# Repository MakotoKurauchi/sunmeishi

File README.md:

# sun meishi

## これは

Kailh Sun Switchを使用した名刺サイズのマクロパッドです。
ロータリーエンコーダもLEDが入っているのでカラフルに光ります。

## 課題

現状でも動作には問題ありませんが、LEDドライバをISSIのデバイスに変えたいと思っています。

## Data
* [Firmware](https://github.com/MakotoKurauchi/qmk_firmware/tree/sunmeishi/keyboards/sunmeishi)
* [PCB Data](/PCB)

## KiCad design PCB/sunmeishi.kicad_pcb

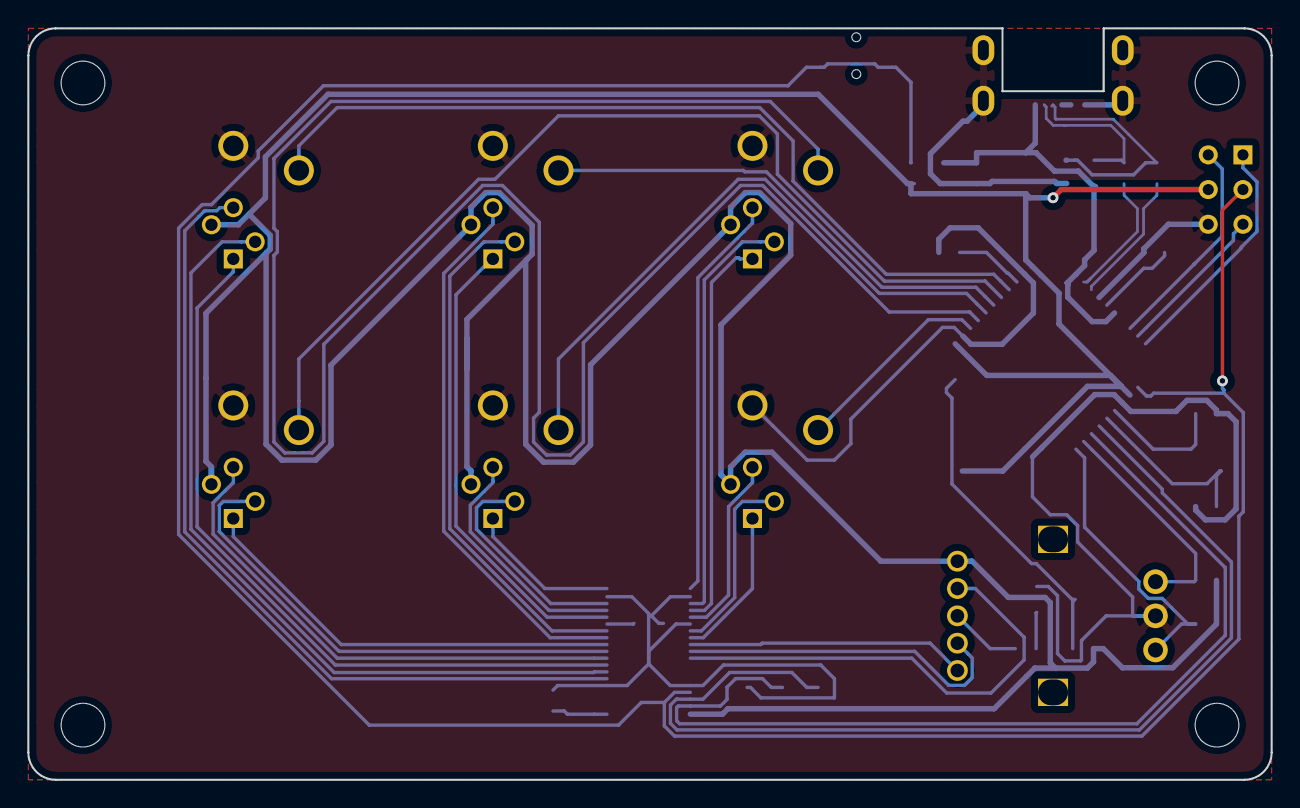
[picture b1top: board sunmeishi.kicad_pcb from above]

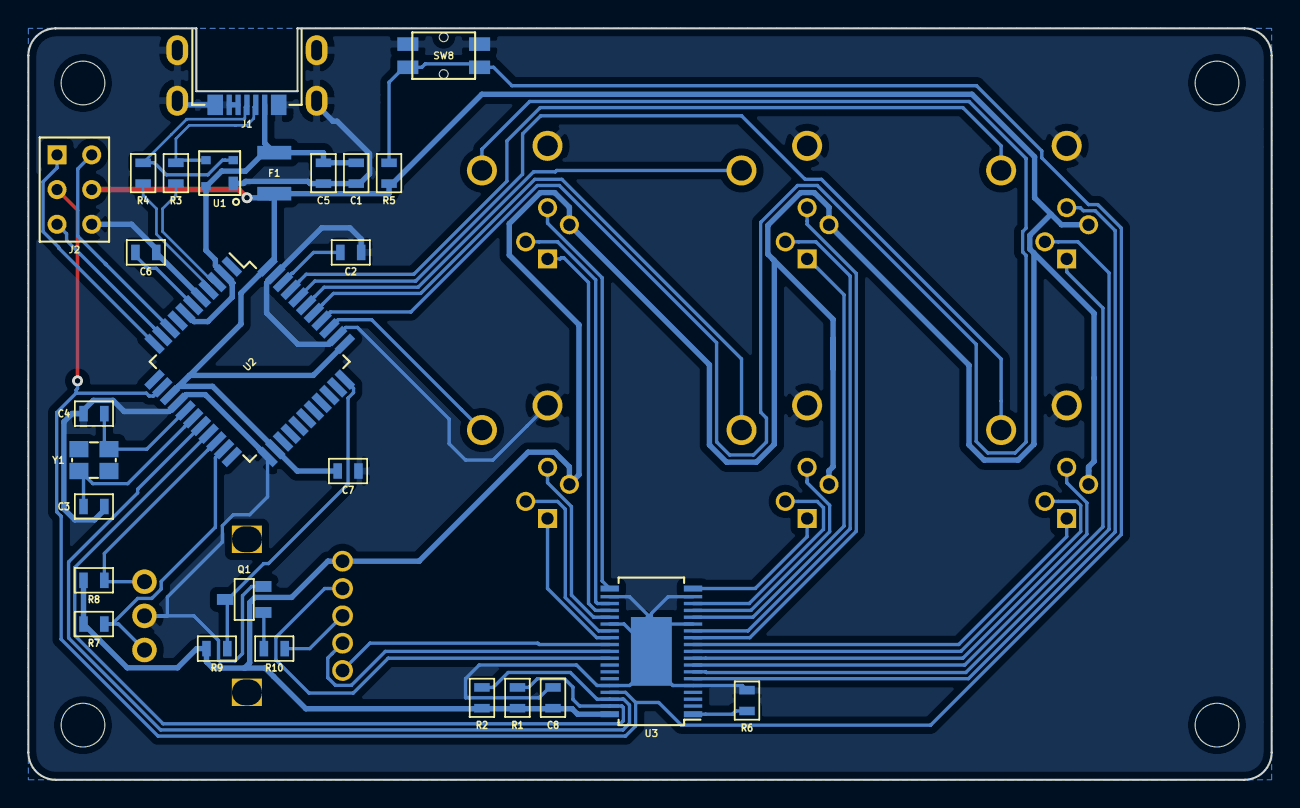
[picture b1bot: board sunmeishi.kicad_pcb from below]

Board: 2 copper layers, 91.0 x 55.0 mm, 44 parts (27 on the bottom side), 50 nets.

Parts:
C1: 10u; SM0603_C
C2, C5, C7, C8: 0.1u; SM0603_C
C3, C4: 22p; SM0603_C
C6: 1u; SM0603_C
F1: FUSE; POLYSWITCH_MICRO_SMD
HOLE_3M, HOLE_3M#2, HOLE_3M#3, HOLE_3M#4: VAL**; HOLE_3M
J1: USB_3; USB_MicroB_609-4049-1-ND
J2: Conn_02x03_Top_Bottom; MY_SIL-2x3
LED1, LED2, LED3, LED4, LED5, LED6: F_LED_A_MINI3; BZPG1583-08002-A1
Q1: 2SC2712
R1, R2: 4.7K; SM0603_R
R3, R4: 22; SM0603_R
R5, R7, R8: 10K; SM0603_R
R6: 2K; SM0603_R
R9, R10: 1K; SM0603_R
SW1, SW2, SW3, SW4, SW5, SW6: SW_Push_45deg; CPG1511B01D03
SW7: EC12PLRGBSDVBF-D-25K-24-24C-61
SW8: SW_Push; TACTSWITCH_ATD-THAF01_SMD
U1: PRTR5V0U2X; SOT143B
U2: ATMEGA32U4_; LQFP-44_10x10mm_Pitch0.8mm
U3: PCA9956ATW; PCA9956BTW
Y1: Crystal; FA-238

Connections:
+5V: C7.1, C8.1, F1.2, J2.4, LED1.2, LED2.2, LED3.2, LED4.2, LED5.2, LED6.2, R1.1, R2.1, R5.2, R7.1, R8.1, R9.1, SW7.5, U2.14, U2.24, U2.34, U2.44, U3.38
/A: R7.2, SW7.A, U2.21
/B: R8.2, SW7.B, U2.20
/COL0: SW1.2, U2.41
/COL1: SW2.2, U2.40
/COL2: SW3.2, U2.39
/COL3: SW4.2, U2.38
/COL4: SW5.2, U2.37
/COL5: SW6.2, U2.36
/COL6: Q1.3, R9.2, U2.33
/L0: LED1.1, U3.6
/L1: LED1.3, U3.7
/L2: LED1.4, U3.8
/L3: LED2.1, U3.9
/L4: LED2.3, U3.10
/L5: LED2.4, U3.11
/L6: LED3.1, U3.12
/L7: LED3.3, U3.13
/L8: LED3.4, U3.15
/L9: LED4.1, U3.16
/L10: LED4.3, U3.17
/L11: LED4.4, U3.19
/L12: LED5.1, U3.20
/L13: LED5.3, U3.22
/L14: LED5.4, U3.23
/L15: LED6.1, U3.24
/L16: LED6.3, U3.26
/L17: LED6.4, U3.27
/L18: SW7.1, U3.28
/L19: SW7.2, U3.29
/L20: SW7.4, U3.30
/MISO: J2.1, U2.11
/MOSI: J2.5, U2.10
/R2C+: R3.1, U2.3
/R2C-: R4.1, U2.4
/SCK: J2.2, U2.9
/U2R+: J1.2, R3.2, U1.3
/U2R-: J1.3, R4.2, U1.2
/VBUS: C1.1, C5.1, F1.1, J1.1, U1.4, U2.2, U2.7
/~RESET: J2.3, R5.1, SW8.1, U2.13, U3.35
GND: C1.2, C2.2, C3.2, C4.2, C5.2, C6.2, C7.2, C8.2, J1.5, J2.6, Q1.2, R6.1, SW1.1, SW2.1, SW3.1, SW4.1, SW5.1, SW6.1, SW7.C, SW8.2, U1.1, U2.5, U2.15, U2.23, U2.35, U2.43, U3.5, U3.14, U3.18, U3.21, U3.25, U3.34
unnamed: C2.1, U2.42
unnamed: C3.1, U2.17, Y1.1
unnamed: C4.1, U2.16, Y1.2
unnamed: C6.1, U2.6
unnamed: Q1.1, R10.2
unnamed: R6.2, U3.1
unnamed: R10.1, SW7.3
SCL: R2.2, U2.18, U3.36
SDA: R1.2, U2.19, U3.37

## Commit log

2020-02-22 add cache files
